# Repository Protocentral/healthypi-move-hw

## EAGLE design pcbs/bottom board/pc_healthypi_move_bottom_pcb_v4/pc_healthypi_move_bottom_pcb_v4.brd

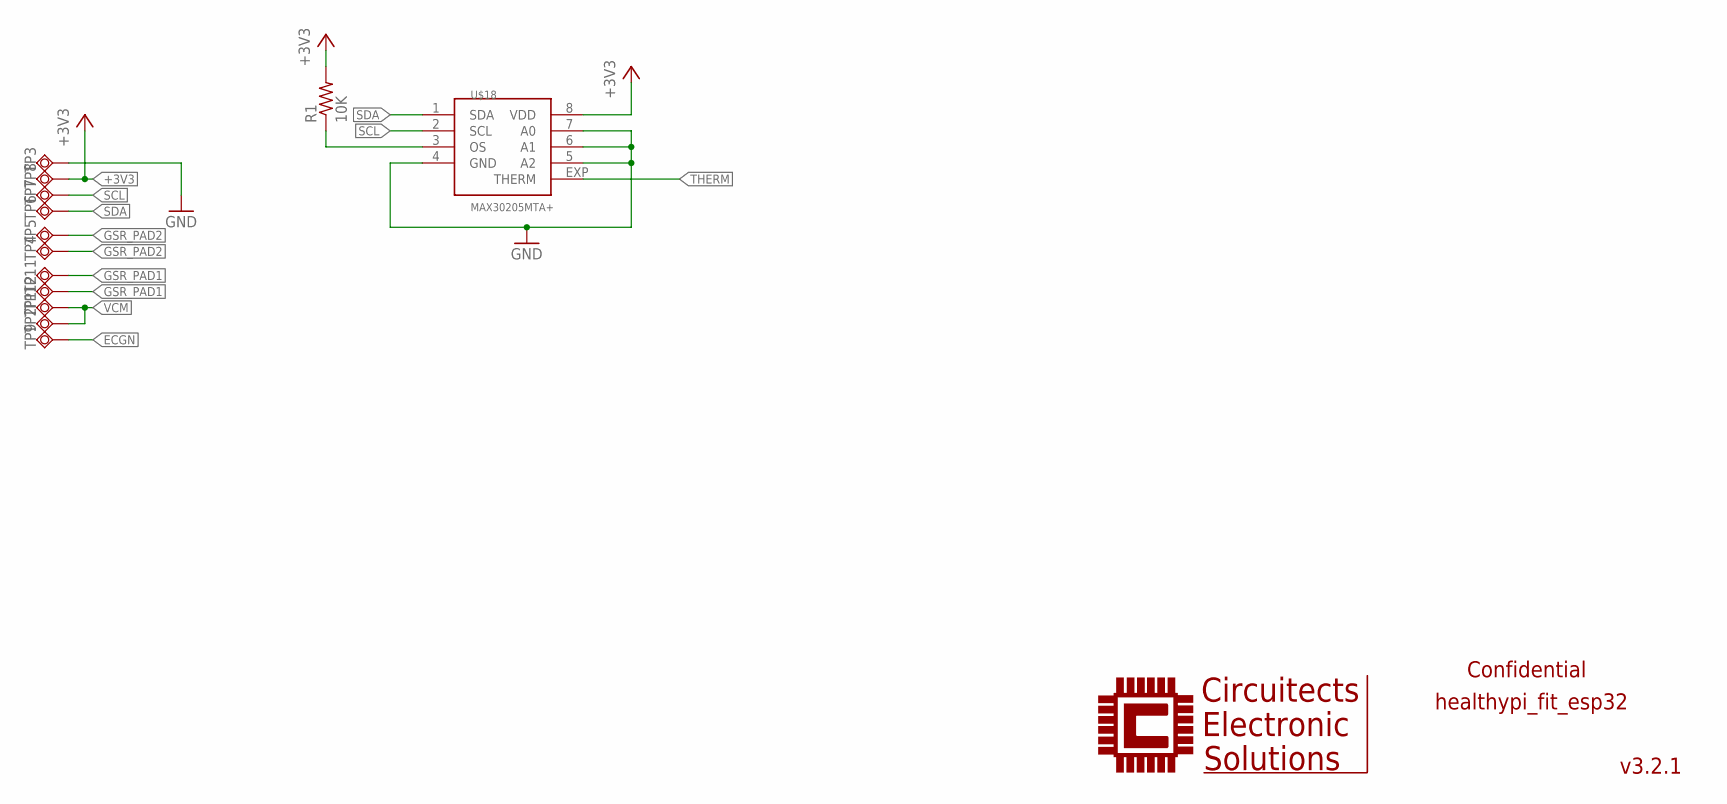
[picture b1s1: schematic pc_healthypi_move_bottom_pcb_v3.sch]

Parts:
R1: 10K; R0201
TP1, TP2, TP3, TP4, TP5, TP6, TP7, TP8, TP9, TP11, TP12: TPSQTP20SQ; TP20SQ
U$18: MAX30205MTA+; TDFN-08

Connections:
+3V3: R1.2, TP8.TP, U$18.8 (VDD)
ECGN: TP9.TP
GND: TP3.TP, U$18.4 (GND), U$18.5 (A2), U$18.6 (A1), U$18.7 (A0)
GSR_PAD1: TP11.TP, TP12.TP
GSR_PAD2: TP4.TP, TP5.TP
unnamed: R1.1, U$18.3 (OS)
SCL: TP7.TP, U$18.2 (SCL)
SDA: TP6.TP, U$18.1 (SDA)
THERM: U$18.EXP (THERM)
VCM: TP1.TP, TP2.TP

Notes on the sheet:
v3.2.1
healthypi_fit_esp32
Confidential

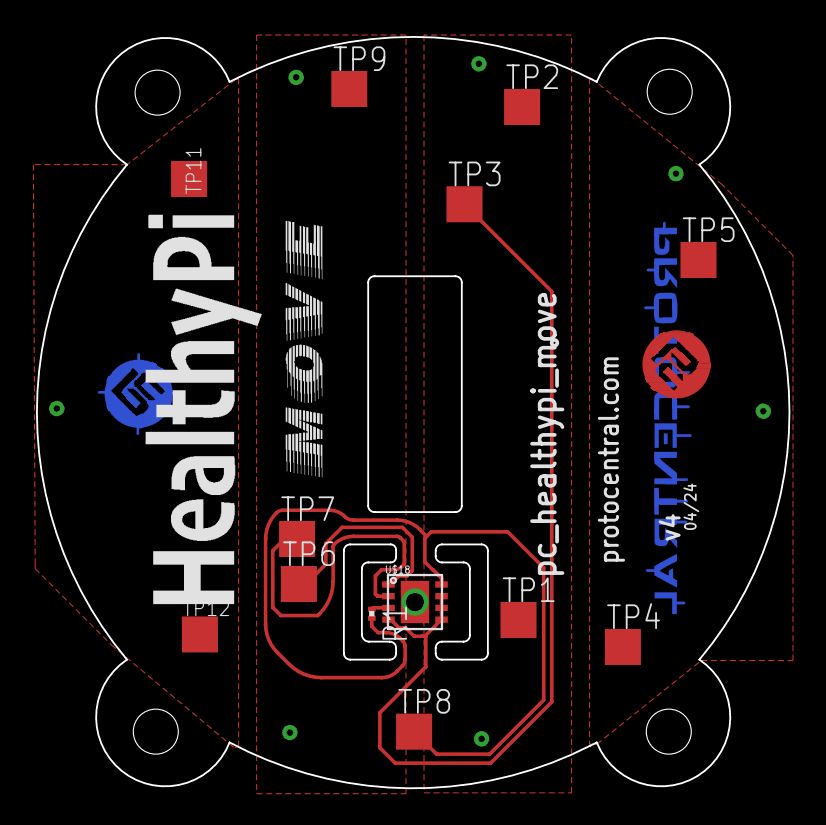
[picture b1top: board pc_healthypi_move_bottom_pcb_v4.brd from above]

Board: 2 copper layers, 41.8 x 41.7 mm, 18 parts (2 on the bottom side), 8 nets.

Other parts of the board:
U$1, U$51: PCROUNDLOGO_GOLD
U$2: HEALTHYPI_MOVE_LOGO
U$3: HEALTHYPI_MOVE_LOGO_1
U$4: PC_LOGO_NAME
